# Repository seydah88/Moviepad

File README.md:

# Moviepad 🎬🥞

A 3-key Breakfast-themed macropad with a rotary encoder that uses KMK firmware!

## Why'd I make it

I wanted to create a keyboard that can be used for controls when you're watching a movie or TV show on your laptop. The waffles and pancakes are inspired by my morning routine, since I often watch a show on my laptop while making breakfast! I also wanted to get experience working with hardware, so I thought this would be a great start!

## BOM
- XIAO RP2040
- 3x Cherry MX Switches
- 3x Blank DSA Keycaps
- Rotary Encoder
- 6x M3 Heatset
- 6x M3x16 Bolt

## CAD Model

## Schematic

## PCB

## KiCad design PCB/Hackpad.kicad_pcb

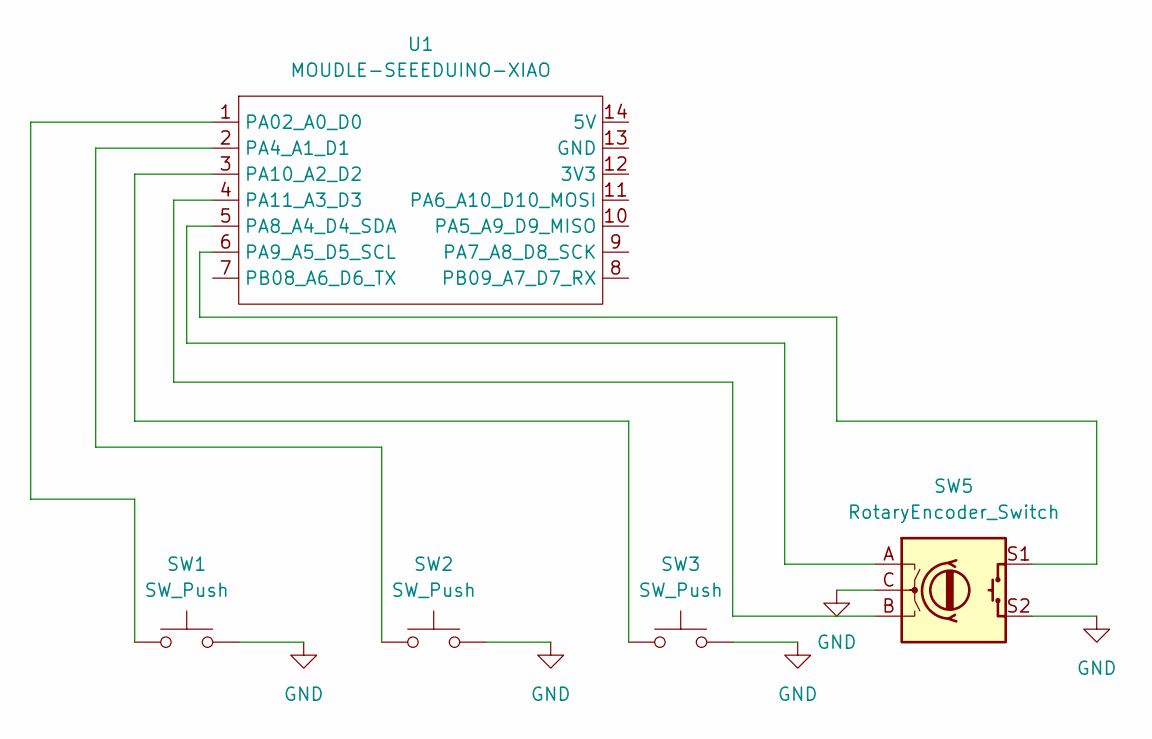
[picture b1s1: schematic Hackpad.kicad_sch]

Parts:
SW1, SW2, SW3: SW_Push
SW5: RotaryEncoder_Switch
U1: MOUDLE-SEEEDUINO-XIAO

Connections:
GND: SW1.2, SW2.2, SW3.2, SW5.C, SW5.S2, U1.13 (GND)
unnamed: SW1.1, U1.1 (PA02_A0_D0)
unnamed: SW2.1, U1.2 (PA4_A1_D1)
unnamed: SW5.A, U1.5 (PA8_A4_D4_SDA)
unnamed: SW5.S1, U1.6 (PA9_A5_D5_SCL)
unnamed: SW3.1, U1.3 (PA10_A2_D2)
unnamed: SW5.B, U1.4 (PA11_A3_D3)

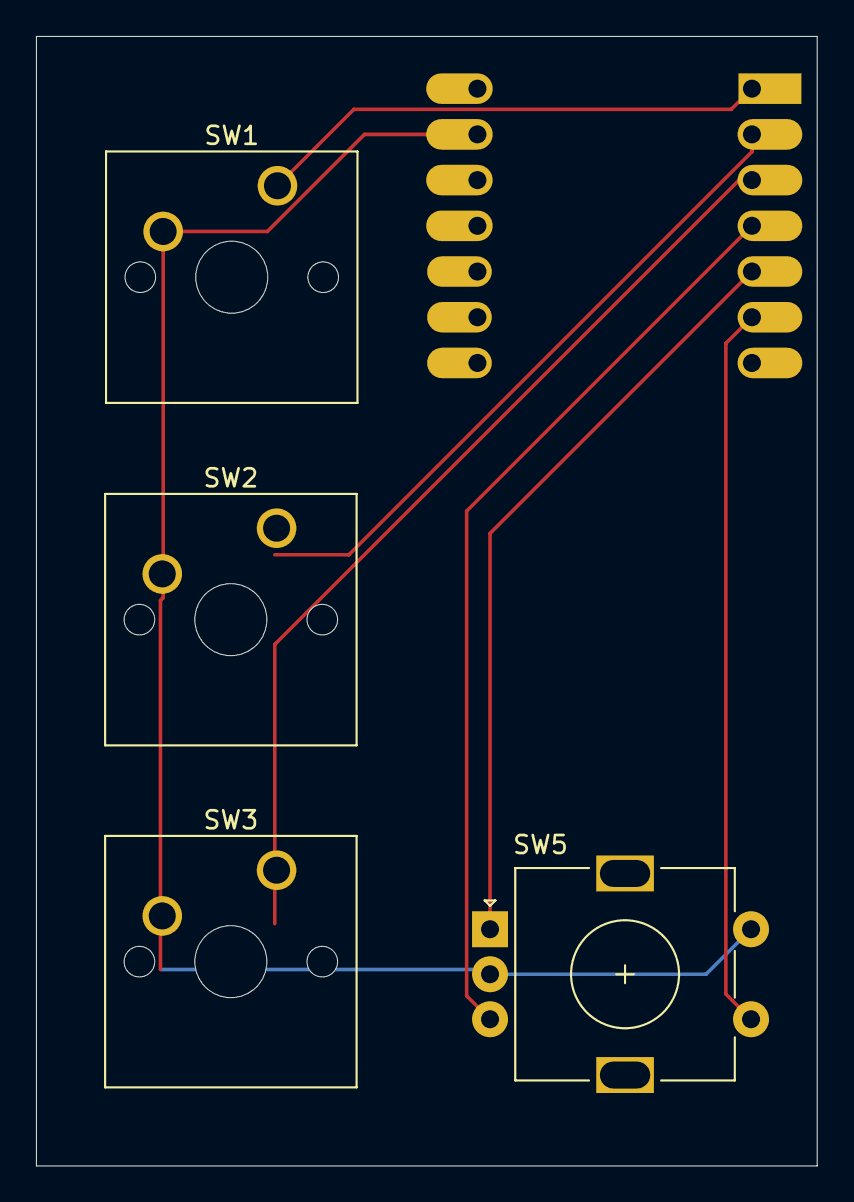
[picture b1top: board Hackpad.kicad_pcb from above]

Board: 2 copper layers, 43.4 x 62.8 mm, 5 parts (1 on the bottom side), 7 nets.
